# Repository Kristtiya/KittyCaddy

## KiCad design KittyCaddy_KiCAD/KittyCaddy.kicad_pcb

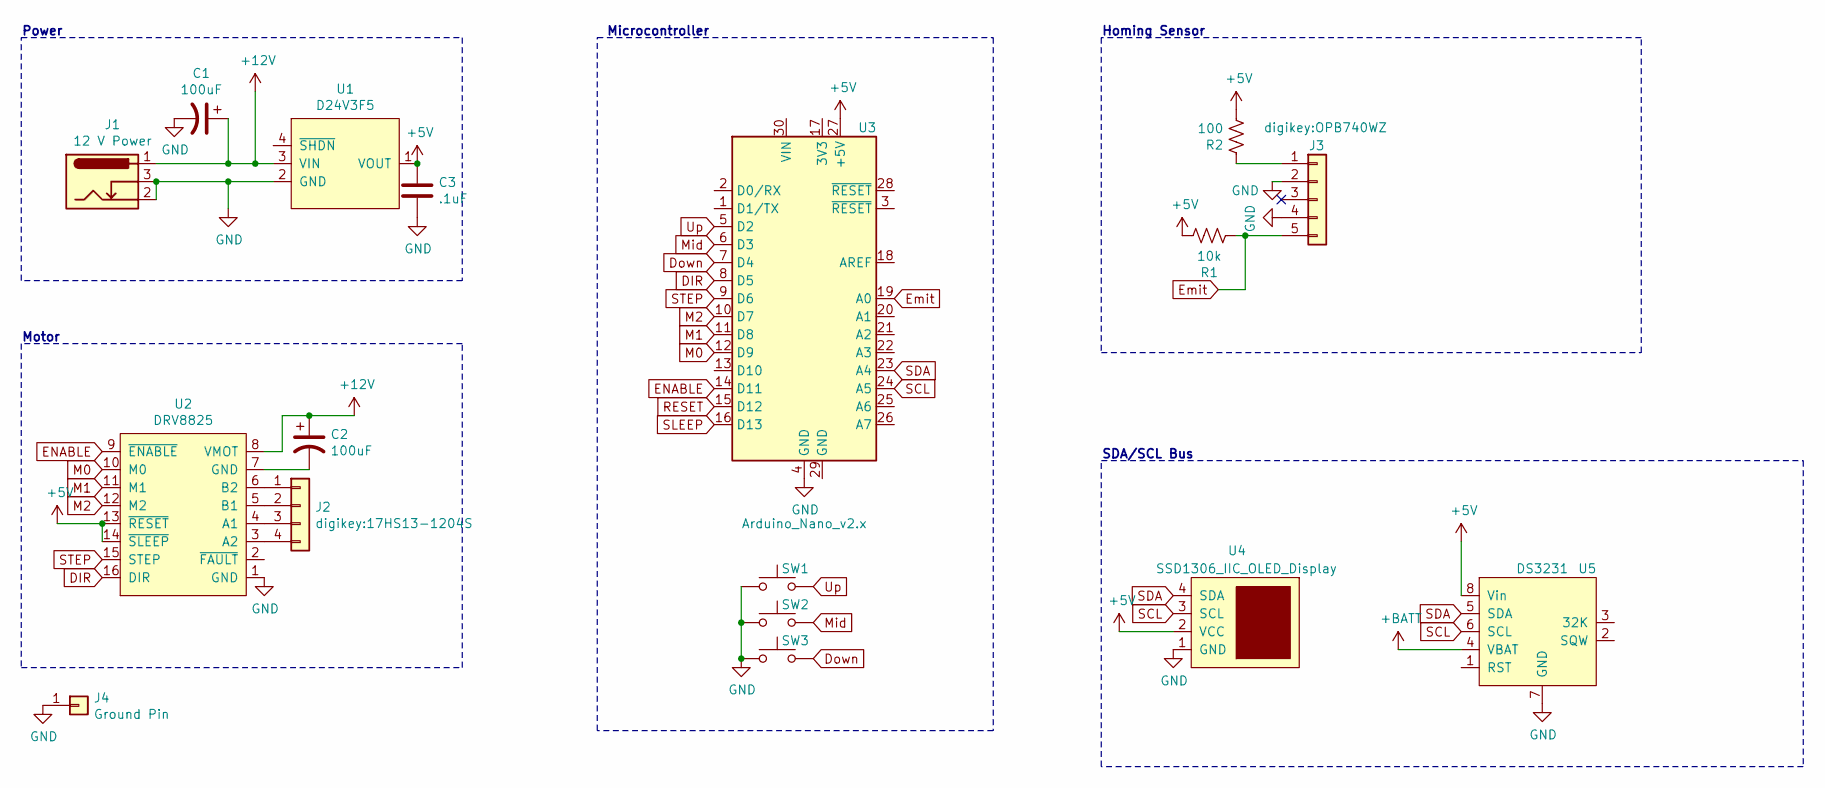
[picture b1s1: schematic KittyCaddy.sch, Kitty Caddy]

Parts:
C1, C2: 100uF; CP_Radial_D8.0mm_P3.50mm
C3: .1uF; 1C10Z5U104M050B
J1: 12 V Power; BarrelJack_Horizontal
J2: digikey:17HS13-1204S; Molex_KK-254_AE-6410-04A_1x04_P2.54mm_Vertical
J3: digikey:OPB740WZ; Molex_KK-254_AE-6410-05A_1x05_P2.54mm_Vertical
J4: Ground Pin; Pin_D1.0mm_L10.0mm_LooseFit
R1: 10k; CF14JT10K0
R2: 100; CFR-25JT-52-100R
SW1, SW2, SW3: SW_Push; DigikeyEG1833-ND
U1: D24V3F5
U2: DRV8825; Pololu_Breakout-16_15.2x20.3mm
U3: Arduino_Nano_v2.x; Arduino_Nano
U4: SSD1306_IIC_OLED_Display; IIC_Display
U5: DS3231

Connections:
+5V: C3.1, R1.1, R2.2, U1.1 (VOUT), U2.13 (~RESET), U2.14 (~SLEEP), U3.27 (+5V), U4.2 (VCC), U5.8 (Vin)
+12V: C1.1, C2.1, J1.1, U1.3 (VIN), U2.8 (VMOT)
+BATT: U5.4 (VBAT)
DIR: U2.16 (DIR), U3.8 (D5)
Down: SW3.2, U3.7 (D4)
ENABLE: U2.9 (~ENABLE), U3.14 (D11)
Emit: J3.5, R1.2, U3.19 (A0)
GND: C1.2, C3.2, J1.2, J1.3, J3.2, J3.4, J4.1, SW1.1, SW2.1, SW3.1, U1.2 (GND), U2.1 (GND), U3.4 (GND), U4.1 (GND), U5.7 (GND)
M0: U2.10 (M0), U3.12 (D9)
M1: U2.11 (M1), U3.11 (D8)
M2: U2.12 (M2), U3.10 (D7)
Mid: SW2.2, U3.6 (D3)
unnamed: C2.2, U2.7 (GND)
unnamed: J2.1, U2.6 (B2)
unnamed: J2.2, U2.5 (B1)
unnamed: J2.3, U2.4 (A1)
unnamed: J2.4, U2.3 (A2)
unnamed: J3.1, R2.1
RESET: U3.15 (D12)
SCL: U3.24 (A5), U4.3 (SCL), U5.6 (SCL)
SDA: U3.23 (A4), U4.4 (SDA), U5.5 (SDA)
SLEEP: U3.16 (D13)
STEP: U2.15 (STEP), U3.9 (D6)
Up: SW1.2, U3.5 (D2)

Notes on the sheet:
Power
Microcontroller
SDA/SCL Bus
Homing Sensor
Motor

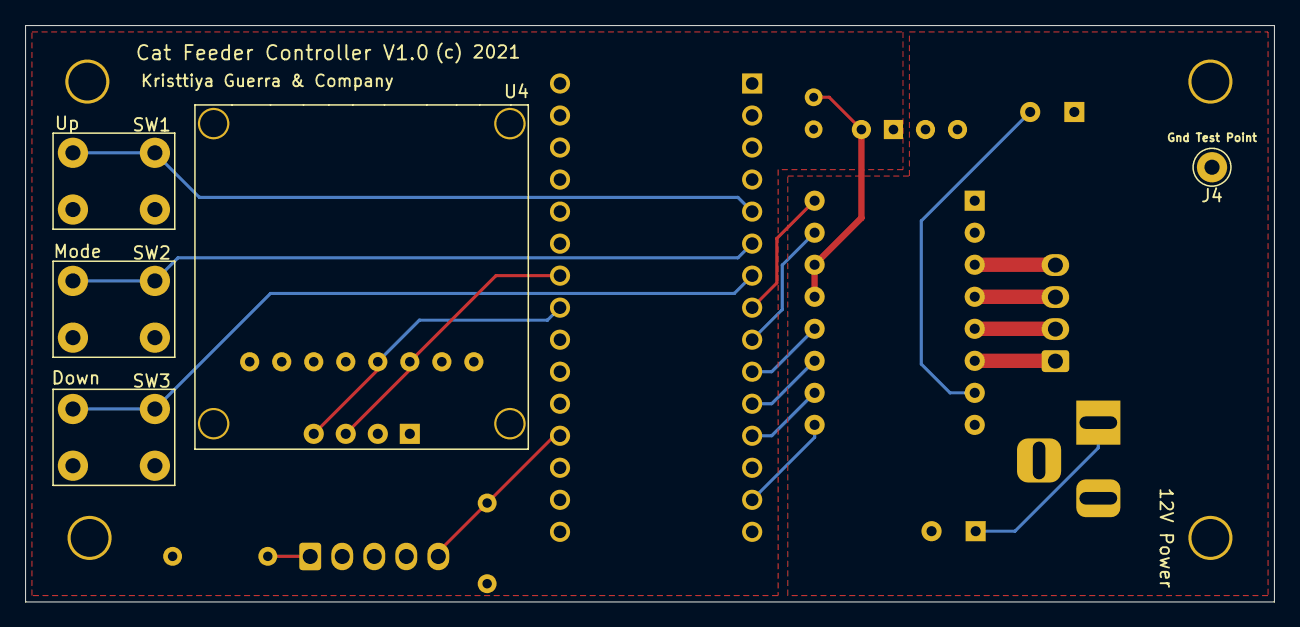
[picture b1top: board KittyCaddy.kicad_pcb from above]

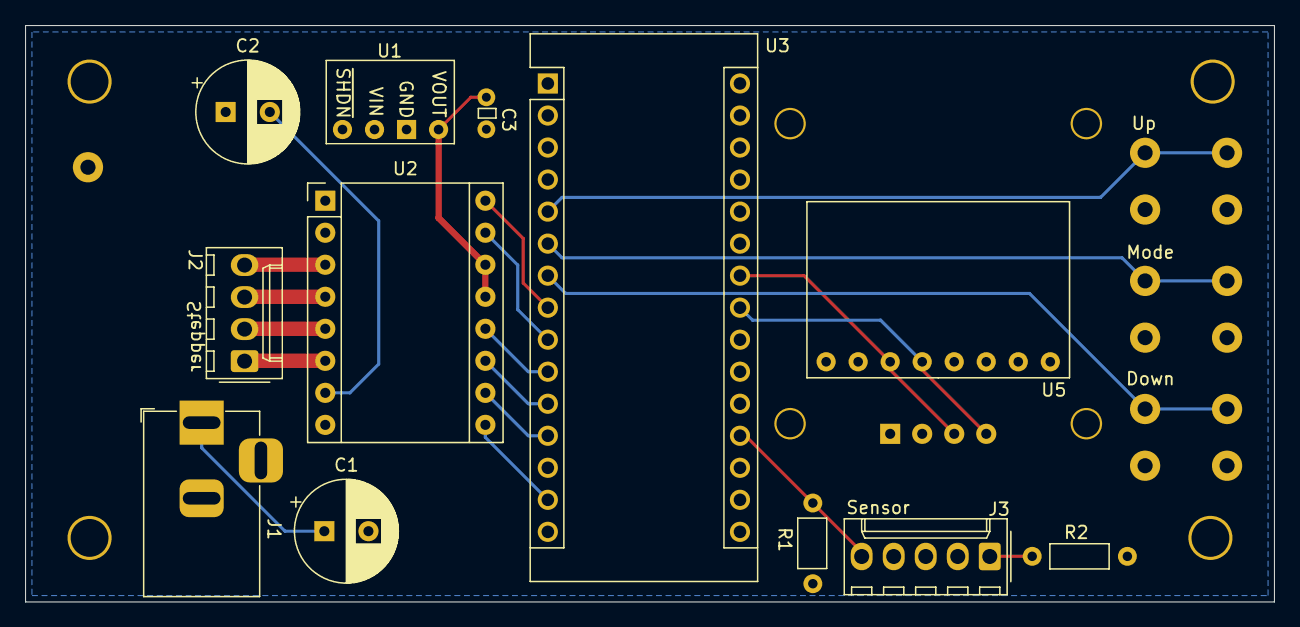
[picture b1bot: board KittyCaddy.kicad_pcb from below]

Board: 2 copper layers, 99.1 x 45.7 mm, 17 parts (12 on the bottom side), 21 nets.

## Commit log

2021-12-18 Upload Project
2021-12-27 Update Button code: Can now determine if Menu button is held or pressed for a short duration of time.
2021-12-27 Fixed Menu screen: Allows selection of Feeder mode with menu button
2021-12-30 Update to working code. EEPROM memory used to store alarm time
2021-12-30 Fixed time increment looping
2021-12-30 Modified button function to be debouncing function
2021-12-30 Fixed enable motor function

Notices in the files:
KittyCaddy_KiCAD/KittyCaddy.kicad_pcb:
(c) 2021
